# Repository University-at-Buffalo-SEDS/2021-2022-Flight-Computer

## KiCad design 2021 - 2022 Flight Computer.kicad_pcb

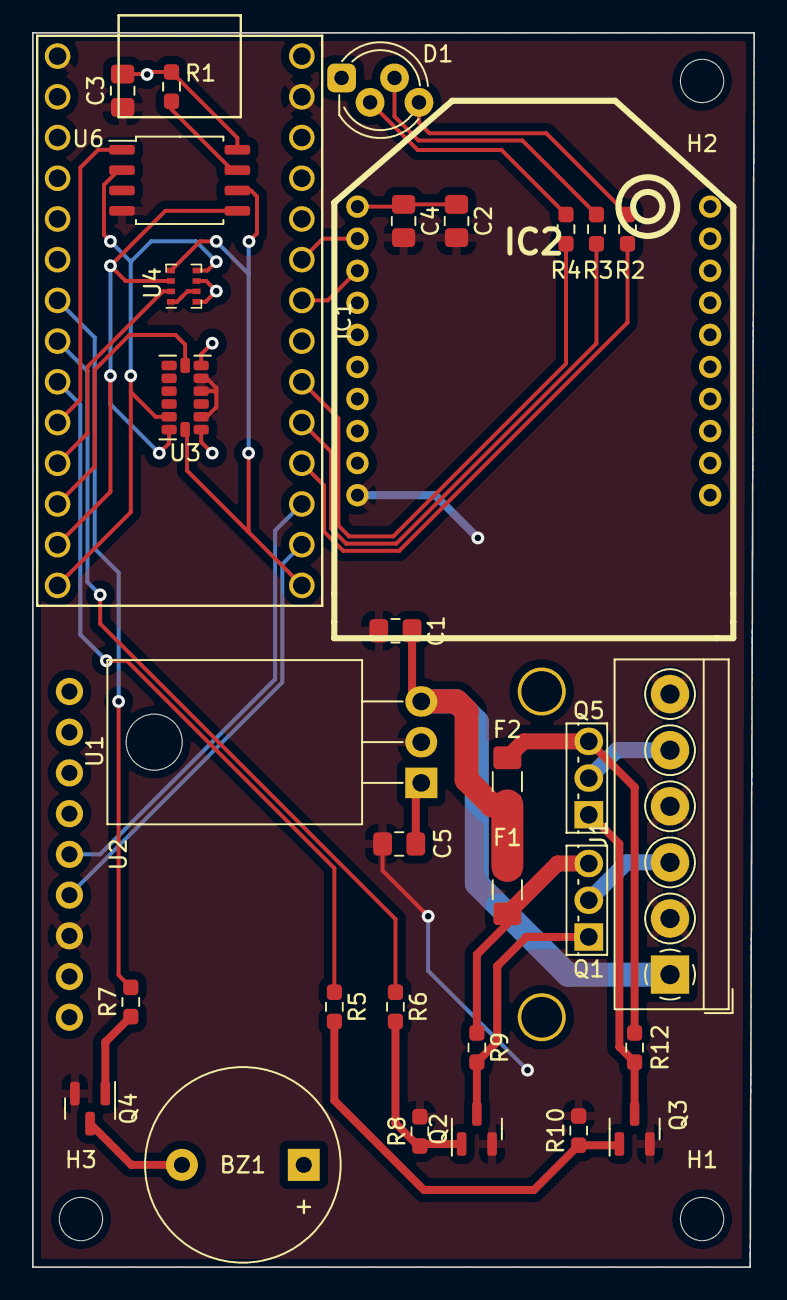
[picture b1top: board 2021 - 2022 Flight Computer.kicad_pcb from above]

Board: 2 copper layers, 45.0 x 77.0 mm, 37 parts (0 on the bottom side), 33 nets.

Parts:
BZ1: Buzzer; Buzzer_12x9.5RM7.6
C1, C5: 10uf; C_0805_2012Metric_Pad1.18x1.45mm_HandSolder
C2: 1uf; C_0805_2012Metric_Pad1.18x1.45mm_HandSolder
C3: 22uf; C_0805_2012Metric_Pad1.18x1.45mm_HandSolder
C4: 47pf; C_0805_2012Metric_Pad1.18x1.45mm_HandSolder
D1: LED_ABGR; LED_D5.0mm-4_RGB_Staggered_Pins
F1, F2: 3A Polyfuse; Fuse_1206_3216Metric_Pad1.42x1.75mm_HandSolder
G1: UB-SEDS-Logo; SEDS_logo_soldermask
H1, H2, H3: MountingHole; MountingHole_2.7mm_M2.5
IC1: TEENSY_4.0; Teensy40
IC2: XB24CZ7PIT-004; XBEE_PRO_PTH
J1: Screw_Terminal_01x06; TerminalBlock_4Ucon_1x06_P3.50mm_Horizontal
Q1, Q5: AOI21357; TO-251-3_Vertical
Q2, Q3, Q4: 2N7002; SOT-23
R1: 10M; R_0603_1608Metric_Pad0.98x0.95mm_HandSolder
R2, R3, R4: 220; R_0603_1608Metric_Pad0.98x0.95mm_HandSolder
R5, R6: 100R; R_0603_1608Metric_Pad0.98x0.95mm_HandSolder
R7: 100; R_0603_1608Metric_Pad0.98x0.95mm_HandSolder
R8, R9, R10, R12: 10k; R_0603_1608Metric_Pad0.98x0.95mm_HandSolder
U1: VXO7803-1000; TO-220-3_Horizontal_TabDown
U2: Flight-Computer_Adafruit_GPS_THT; Adafruit_GPS_THT
U3: ADXL345; LGA-14_3x5mm_P0.8mm_LayoutBorder1x6y
U4: BMP280; Bosch_LGA-8_2x2.5mm_P0.65mm_ClockwisePinNumbering
U6: Memory_Flash_W25Q32JVSS; SOIC-8_5.23x5.23mm_P1.27mm

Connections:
+3V3: BZ1.1 (-), C2.1, C3.2, C4.1, C5.1, D1.1 (A), IC1.31 (3.3V(250_MA_MAX)), IC2.1 (VCC), R1.1, U1.1 (VOUT), U2.8 (VIN), U3.1 (Vdd_I/O), U3.6 (Vs), U4.6 (VDDIO), U4.8 (VDD), U6.8 (VCC)
+BATT: C1.1, F1.1, F2.1, J1.1, U1.3 (VIN)
/ACT1: IC1.8 (6), R6.1
/ACT2: IC1.9 (7), R5.1
/DROGUE_POW: J1.3, Q1.2 (D)
/GPS.RX: IC1.21 (14), U2.6 (RX)
/GPS.TX: IC1.22 (15), U2.5 (TX)
/MAIN_POW: J1.5, Q5.2 (D)
/SPI.ADXL-CS: IC1.12 (10), U3.7 (~CS)
/SPI.BMP-CS: IC1.11 (9), U4.2 (CSB)
/SPI.FL-CS: IC1.10 (8), U6.1 (~CS)
/SPI.MISO: IC1.14 (12), U3.12 (SDO/ADDR), U4.5 (SDO), U6.2 (DO(IO1))
/SPI.MOSI: IC1.13 (11), U3.13 (SDA/SDI/SDIO), U4.3 (SDI), U6.5 (DI(IO0))
/SPI.SCK: IC1.20 (13), U3.14 (SCL/SCLK), U4.4 (SCK), U6.6 (CLK)
/XBEE.RX: IC1.27 (20), IC2.3 (DIN/~CONFIG)
/XBEE.TX: IC1.28 (21), IC2.2 (DOUT)
BUZZER: IC1.7 (5), R7.2
GND: C1.2, C2.2, C3.1, C4.2, C5.2, IC1.1 (GND_1), IC1.32 (GND_3), IC2.10 (GND), J1.2, J1.4, J1.6, Q2.2 (S), Q3.2 (S), Q4.2 (S), R8.2, R10.2, U1.2 (GND), U2.7 (GND), U3.2 (GND), U3.4 (GND), U3.5 (GND), U4.1 (GND), U4.7 (GND), U6.4 (GND)
LED-B: IC1.25 (18), R4.2
LED-G: IC1.24 (17), R3.2
LED-R: IC1.23 (16), R2.2
unnamed: BZ1.2 (+), Q4.3 (D)
unnamed: D1.2 (BK), R4.1
unnamed: D1.3 (GK), R3.1
unnamed: D1.4 (RK), R2.1
unnamed: F1.2, Q1.3 (S), R9.1
unnamed: F2.2, Q5.3 (S), R12.1
unnamed: Q2.1 (G), R6.2, R8.1
unnamed: Q1.1 (G), Q2.3 (D), R9.2
unnamed: Q3.1 (G), R5.2, R10.1
unnamed: Q3.3 (D), Q5.1 (G), R12.2
unnamed: Q4.1 (G), R7.1
unnamed: R1.2, U6.7 (IO3)

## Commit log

2022-01-07 Removed Everything
    Per Dario's Wish
2022-01-07 Revert "Removed Everything"
    This reverts commit 7913d41127ad5e9af118bf1e851c83a13618c6f2.
2022-01-07 Revert "Revert "Removed Everything""
    This reverts commit 2e047b4e948686c34578e177d58ea0672e58c7b8.
2022-01-07 All schematic files
2022-01-07 Added gitignore and removed redundant files
    .gitignore will help with preventing pushing backup/temp files.
    All the files that were removed were backups/temp
2022-01-20 Added Ignition
2022-01-22 Board Layout (kinda)
2022-02-18 Something
2022-02-18 Pyro Channels
2022-02-19 Pyro channels and power supply mods
2022-02-21 Tried to wire SPI
2022-02-22 Digital wiring
2022-02-23 some capacitors and resistors traced
2022-02-23 Minor optimizations
2022-02-28 Finished tracing (needs optimizing)
2022-03-01 Small optimizations
2022-03-01 Connected some stuff to ground and 3V3
2022-03-01 Small changes
2022-03-01 Cleaned up bus lines, fixed stranded islands
2022-03-01 Fix schematic grid
2022-03-04 Fixed some things
2022-03-04 Updated again
2022-03-04 Updated... Again
2022-03-04 Grid
2022-03-06 Fixed busses
2022-03-06 Power Pins Fixed (***UPDATED PCB***)
    Replaced resistors and mosfet with ones from schematic.
    Might want to roll back to something before this if anything goes wrong.
2022-03-06 Last bus grouping update
2022-03-07 Removed a few hidden unconnected wires
2022-03-11 Checked Parts
2022-03-14 Last Ground Fix
2022-03-14 UB SEDS Logo File
2022-03-18 Added UB SEDS Logo
2022-04-22 Revert "Add files via upload"
    This reverts commit a89c25e643e2f36197d76d802668cdfff43c7fec.
2022-04-22 Reset
2022-04-22 Gerber files added
2022-05-13 Added 3D files
2022-05-30 fix mosfet
2022-05-30 Spaced a few parts
2022-05-30 Unmoved parts cause stencil
2022-05-30 Didnt save before
2022-05-30 Hot fix
2022-06-01 New Gerbers
